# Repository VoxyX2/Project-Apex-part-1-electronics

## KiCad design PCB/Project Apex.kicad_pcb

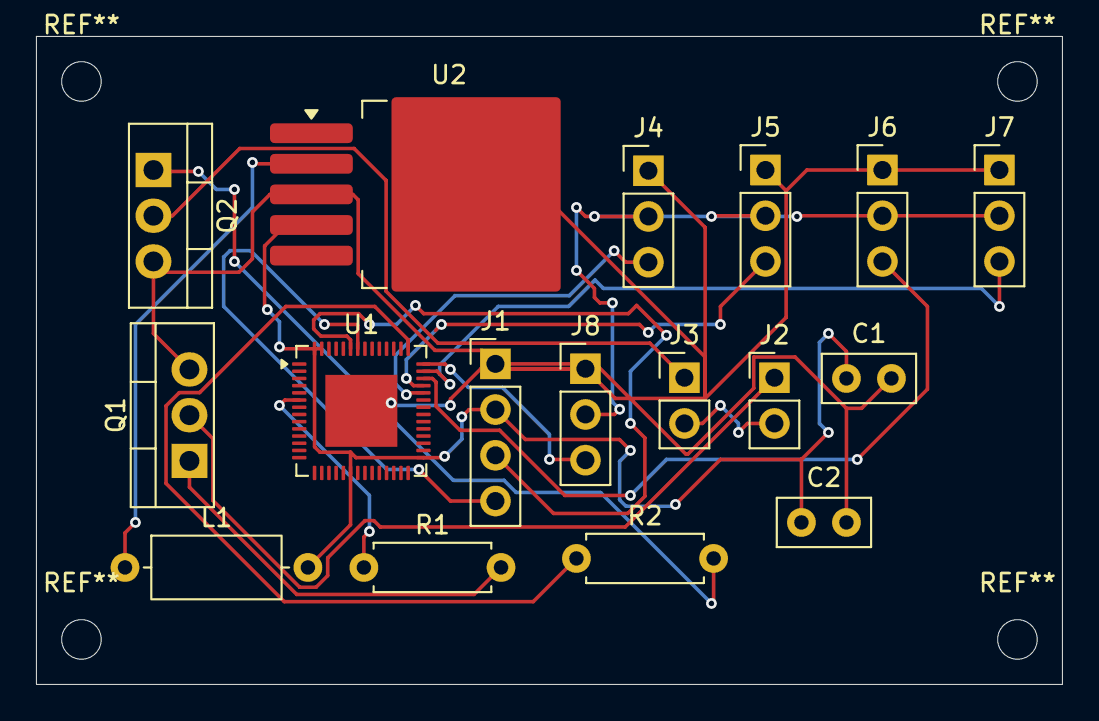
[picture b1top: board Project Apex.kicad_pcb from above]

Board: 2 copper layers, 57.0 x 36.0 mm, 17 parts (0 on the bottom side), 18 nets.

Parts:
C1, C2: C; C_Disc_D5.0mm_W2.5mm_P2.50mm
J1: Conn_01x04_Pin; PinHeader_1x04_P2.54mm_Vertical
J2, J3: Conn_01x02_Pin; PinHeader_1x02_P2.54mm_Vertical
J4, J5, J6, J7, J8: Conn_01x03_Pin; PinHeader_1x03_P2.54mm_Vertical
L1: L; L_Axial_L7.0mm_D3.3mm_P10.16mm_Horizontal_Fastron_MICC
Q1, Q2: IRLZ44N; TO-220-3_Vertical
R1, R2: R; R_Axial_DIN0207_L6.3mm_D2.5mm_P7.62mm_Horizontal
U1: ESP32-S3; QFN-56-1EP_7x7mm_P0.4mm_EP4x4mm
U2: LM2596S-3.3; TO-263-5_TabPin3

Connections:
+3V3: C1.1, C2.1, J1.2, L1.2, U1.20 (VDD3P3_RTC), U1.29 (VDD_SPI), U1.55 (VDDA), U1.56 (VDDA), U2.4 (FB)
+5V: J4.2, J5.2, J6.2, J7.2, J8.2
+12V: J2.2, J3.2
GND: C1.2, C2.2, J1.1, J4.1, J5.1, J6.1, J7.1, J8.1, Q1.3 (S), Q2.3 (S), U1.57 (GND), U2.3 (GND)
unnamed: J1.3, U1.51 (GPIO45)
unnamed: J1.4, U1.50 (U0RXD)
unnamed: J2.1, Q1.2 (D)
unnamed: J3.1, Q2.2 (D)
unnamed: J4.3, U1.38 (GPIO33)
unnamed: J5.3, U1.39 (GPIO34)
unnamed: J6.3, U1.40 (GPIO35)
unnamed: J7.3, U1.41 (GPIO36)
unnamed: J8.3, U1.42 (GPIO37)
unnamed: Q1.1 (G), R1.2
unnamed: Q2.1 (G), R2.2
unnamed: R1.1, U1.6 (GPIO1)
unnamed: R2.1, U1.43 (GPIO38)
unnamed: L1.1, U2.2 (OUT)
